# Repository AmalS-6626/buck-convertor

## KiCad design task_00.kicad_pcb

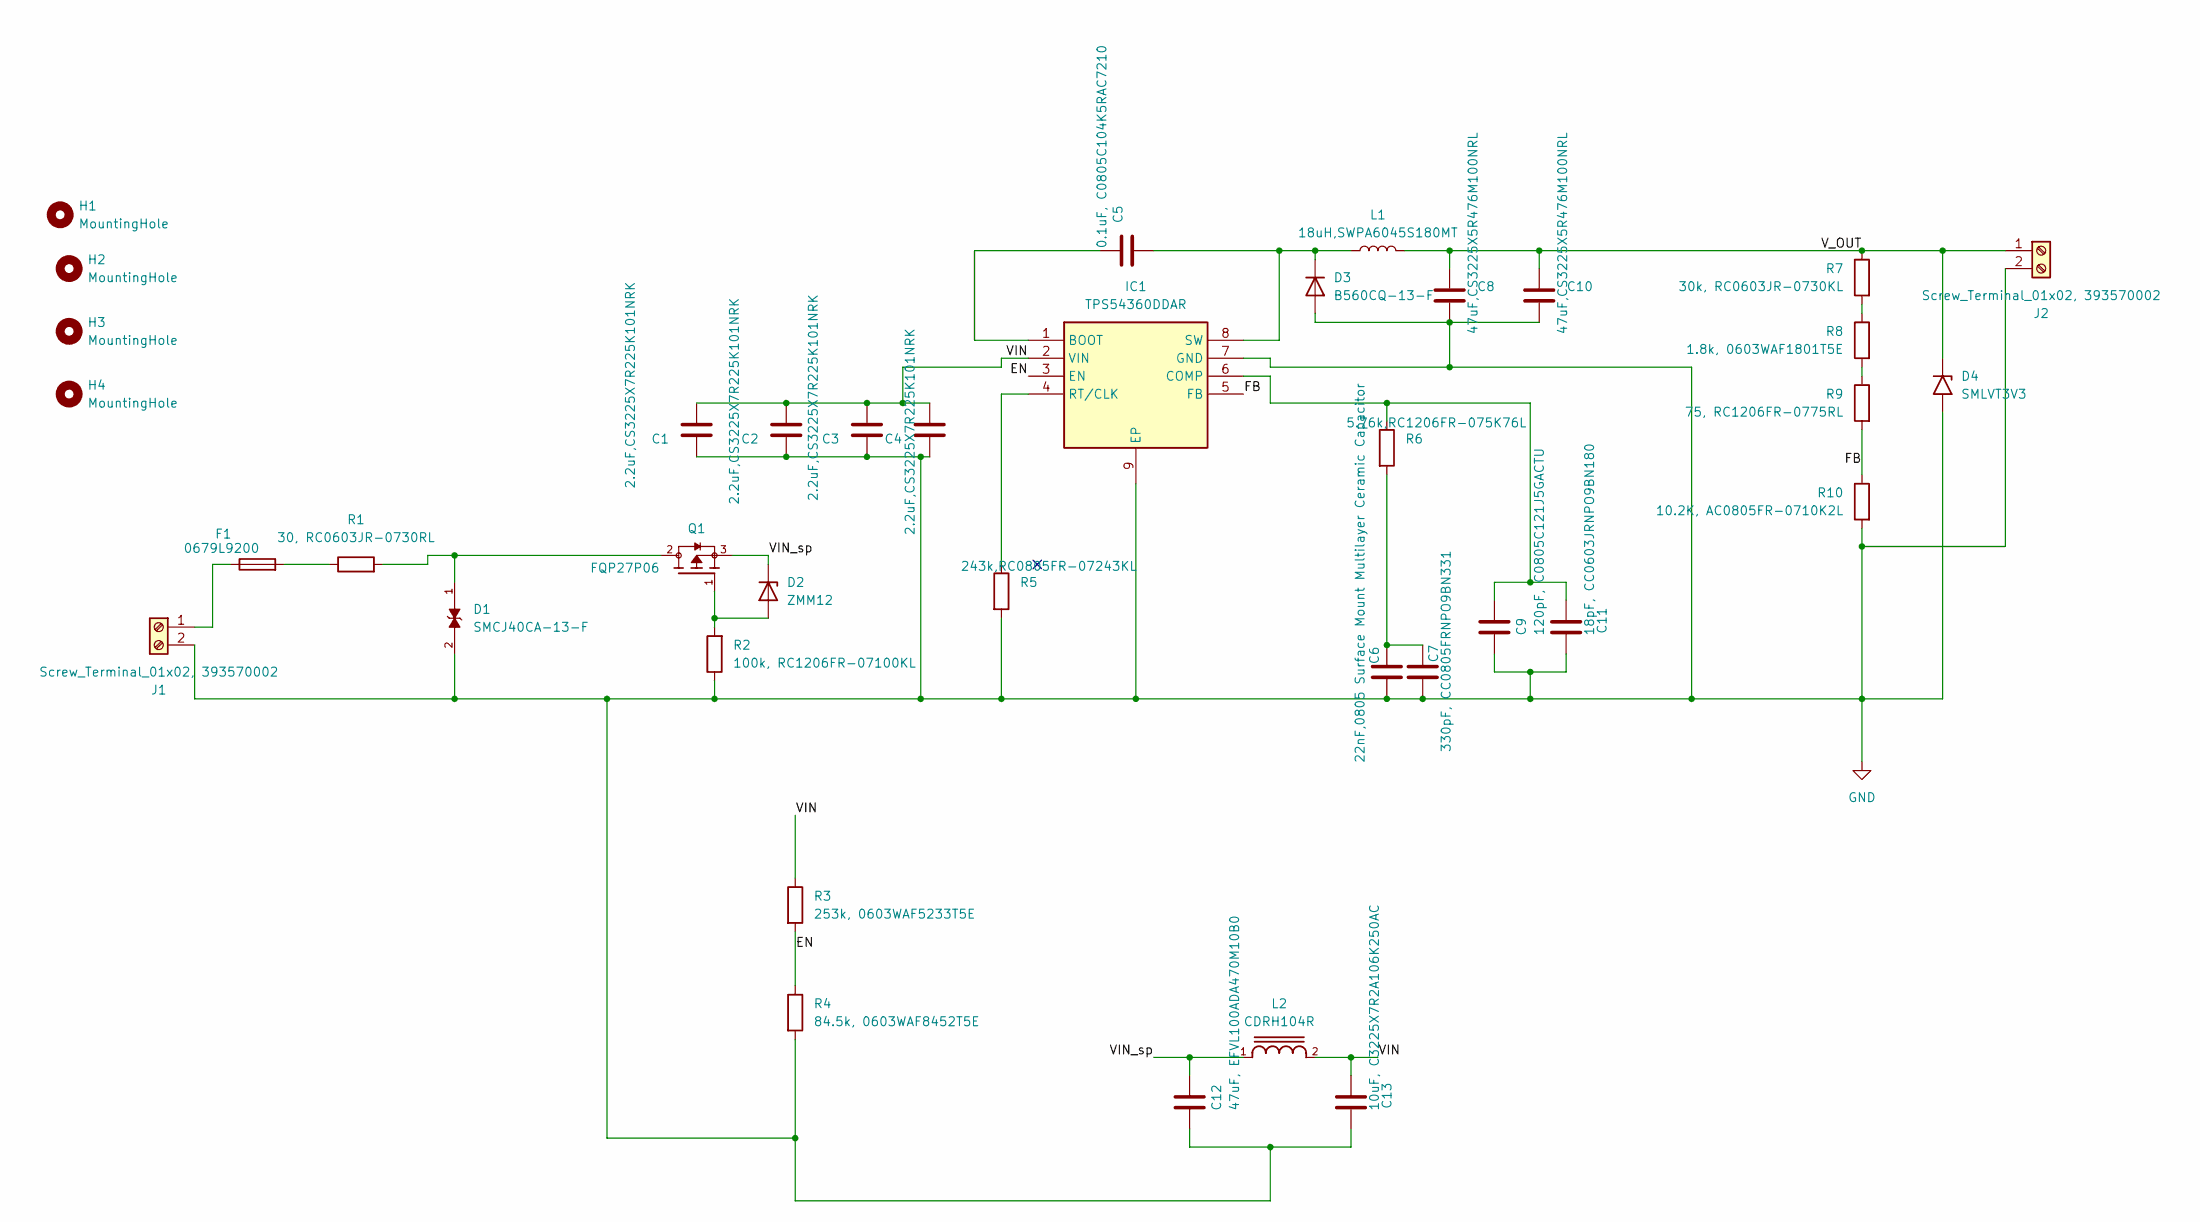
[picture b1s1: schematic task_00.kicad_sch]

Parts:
C1, C2, C3, C4: 2.2uF,CS3225X7R225K101NRK; C_1210_3225Metric_Pad1.33x2.70mm_HandSolder
C5: 0.1uF, C0805C104K5RAC7210; C_0805_2012Metric_Pad1.18x1.45mm_HandSolder
C6: 22nF,0805 Surface Mount Multilayer Ceramic Capaci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; C_0805_2012Metric_Pad1.18x1.45mm_HandSolder
C7: 330pF, CC0805FRNPO9BN331; C_0805_2012Metric_Pad1.18x1.45mm_HandSolder
C8, C10: 47uF,CS3225X5R476M100NRL; C_1210_3225Metric_Pad1.33x2.70mm_HandSolder
C9: 120pF, C0805C121J5GACTU; C_0805_2012Metric_Pad1.18x1.45mm_HandSolder
C11: 18pF, CC0603JRNPO9BN180; C_0603_1608Metric_Pad1.08x0.95mm_HandSolder
C12: 47uF, EFVL100ADA470M10B0; CP_Elec_10x10.5
C13: 10uF, C3225X7R2A106K250AC; C_1210_3225Metric_Pad1.33x2.70mm_HandSolder
D1: SMCJ40CA-13-F; TVS_SMCJ40CA-13-F; PARTREV 19 - 2
D2: ZMM12; P8_DO-213AA_MiniMelf
D3: B560CQ-13-F; B560C-13-F_handsolder
D4: SMLVT3V3; DIOM5336X265N
F1: 0679L9200; FUSC6125X279N
H1, H2, H3, H4: MountingHole; MountingHole_2.1mm
IC1: TPS54360DDAR; SOIC127P600X170-9N; Manufacturer_Part_Number TPS54360DDAR; Mouser Part Number 595-TPS54360DDAR
J1, J2: Screw_Terminal_01x02, 393570002; CONN_393570002_MOL_screwterminal01x02
L1: 18uH,SWPA6045S180MT; SWPA6045S220MT
L2: CDRH104R
Q1: FQP27P06; TO-220; PARTREV C
R1: 30, RC0603JR-0730RL; R_0603_1608Metric_Pad0.98x0.95mm_HandSolder
R2: 100k, RC1206FR-07100KL; R_1206_3216Metric_Pad1.30x1.75mm_HandSolder
R3: 253k, 0603WAF5233T5E; R_0603_1608Metric_Pad0.98x0.95mm_HandSolder
R4: 84.5k, 0603WAF8452T5E; R_0603_1608Metric_Pad0.98x0.95mm_HandSolder
R5: 243k,RC0805FR-07243KL; R_0805_2012Metric_Pad1.20x1.40mm_HandSolder
R6: 5.76k,RC1206FR-075K76L; R_1206_3216Metric_Pad1.30x1.75mm_HandSolder
R7: 30k, RC0603JR-0730KL; R_0603_1608Metric_Pad0.98x0.95mm_HandSolder
R8: 1.8k, 0603WAF1801T5E; R_0603_1608Metric_Pad0.98x0.95mm_HandSolder
R9: 75, RC1206FR-0775RL; R_1206_3216Metric_Pad1.30x1.75mm_HandSolder
R10: 10.2K, AC0805FR-0710K2L; R_0805_2012Metric_Pad1.20x1.40mm_HandSolder

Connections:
/EN: IC1.3 (EN), R3.2, R4.1
/FB: IC1.5 (FB), R9.2, R10.1
/VIN: C1.1, C2.1, C3.1, C4.1, C13.1, IC1.2 (VIN), L2.2, R3.1
/VIN_sp: C12.1, D2.1 (K), L2.1, Q1.3
/V_OUT: C8.1, C10.1, D4.1 (A1), J2.1, L1.2, R7.1
GND: C1.2, C2.2, C3.2, C4.2, C6.2, C7.2, C8.2, C9.2, C10.2, C11.2, C12.2, C13.2, D1.2, D3.2 (A), D4.2 (A2), IC1.7 (GND), IC1.9 (EP), J1.2, J2.2, R2.1, R4.2, R5.2, R10.2
unnamed: C6.1, C7.1, R6.2
unnamed: D1.1, Q1.2, R1.2
unnamed: D2.2 (A), Q1.1, R2.2
unnamed: C5.2, D3.1 (K), IC1.8 (SW), L1.1
unnamed: F1.2, R1.1
unnamed: C5.1, IC1.1 (BOOT)
unnamed: C9.1, C11.1, IC1.6 (COMP), R6.1
unnamed: IC1.4 (RT/CLK), R5.1
unnamed: F1.1, J1.1
unnamed: R7.2, R8.1
unnamed: R8.2, R9.1

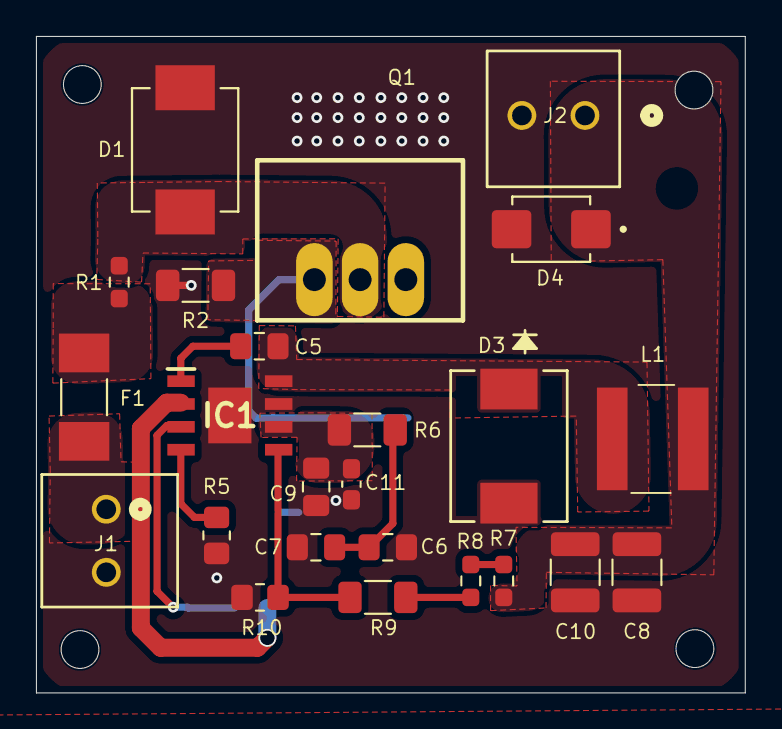
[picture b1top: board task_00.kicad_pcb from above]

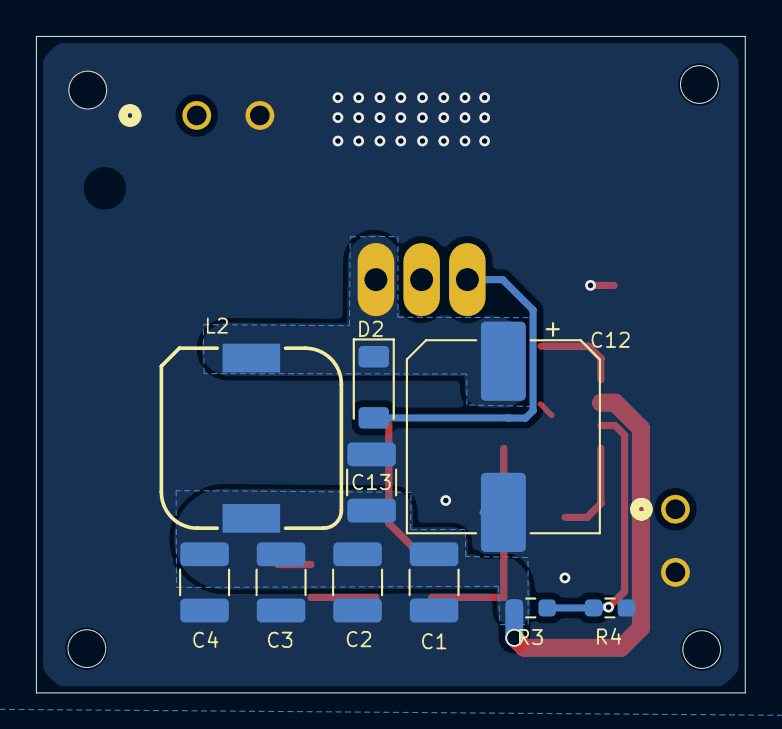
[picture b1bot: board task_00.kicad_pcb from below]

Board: 2 copper layers, 39.4 x 36.5 mm, 38 parts (10 on the bottom side), 17 nets.
